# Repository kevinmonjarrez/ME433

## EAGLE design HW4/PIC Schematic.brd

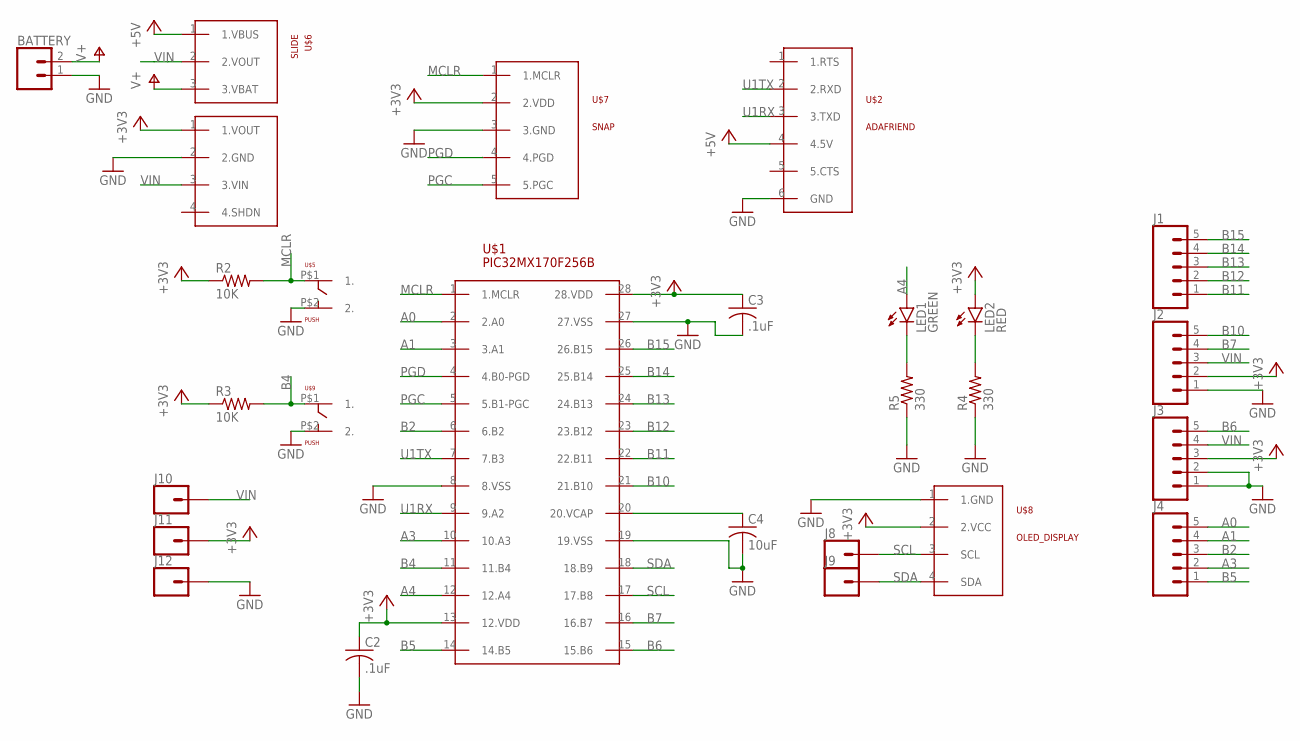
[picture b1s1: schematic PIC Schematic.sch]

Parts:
BATTERY: CONN_02; 1X02
C2, C3: .1uF; C025-030X050
C4: 10uF; C025-030X050
J1, J2, J3, J4: CONN_05; 1X05
J8, J9, J10, J11, J12: CONN_01; 1X01
LED1: GREEN; LED3MM
LED2: RED; LED3MM
R2, R3: 10K; 0207/10
R4, R5: 330; 0207/10
U$1: PIC32MX170F256B; DIL28-3
U$2: ADAFRIEND
U$3: POLOLU_3V3
U$5, U$9: PUSH
U$6: SLIDE
U$7: SNAP
U$8: OLED_DISPLAY

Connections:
+3V3: C2.1, C3.1, J2.2, J3.3, J11.1, LED2.A, R2.1, R3.1, U$1.13 (12.VDD), U$1.28 (28.VDD), U$3.1 (1.VOUT), U$7.2 (2.VDD), U$8.2 (2.VCC)
+5V: U$2.4 (4.5V), U$6.1 (1.VBUS)
A0: J4.5, U$1.2 (2.A0)
A1: J4.4, U$1.3 (3.A1)
A3: J4.2, U$1.10 (10.A3)
A4: LED1.A, U$1.12 (12.A4)
B2: J4.3, U$1.6 (6.B2)
B4: R3.2, U$1.11 (11.B4), U$9.P$1 (1.)
B5: J4.1, U$1.14 (14.B5)
B6: J3.5, U$1.15 (15.B6)
B7: J2.4, U$1.16 (16.B7)
B10: J2.5, U$1.21 (21.B10)
B11: J1.1, U$1.22 (22.B11)
B12: J1.2, U$1.23 (23.B12)
B13: J1.3, U$1.24 (24.B13)
B14: J1.4, U$1.25 (25.B14)
B15: J1.5, U$1.26 (26.B15)
GND: BATTERY.1, C2.2, C3.2, C4.2, J2.1, J3.1, J3.2, J12.1, R4.1, R5.1, U$1.8 (8.VSS), U$1.19 (19.VSS), U$1.27 (27.VSS), U$2.6 (GND), U$3.2 (2.GND), U$5.P$2 (2.), U$7.3 (3.GND), U$8.1 (1.GND), U$9.P$2 (2.)
MCLR: R2.2, U$1.1 (1.MCLR), U$5.P$1 (1.), U$7.1 (1.MCLR)
unnamed: C4.1, U$1.20 (20.VCAP)
unnamed: LED1.K (C), R5.2
unnamed: LED2.K (C), R4.2
PGC: U$1.5 (5.B1-PGC), U$7.5 (5.PGC)
PGD: U$1.4 (4.B0-PGD), U$7.4 (4.PGD)
SCL: J8.1, U$1.17 (17.B8), U$8.3 (SCL)
SDA: J9.1, U$1.18 (18.B9), U$8.4 (SDA)
U1RX: U$1.9 (9.A2), U$2.3 (3.TXD)
U1TX: U$1.7 (7.B3), U$2.2 (2.RXD)
V+: BATTERY.2, U$6.3 (3.VBAT)
VIN: J2.3, J3.4, J10.1, U$3.3 (3.VIN), U$6.2 (2.VOUT)

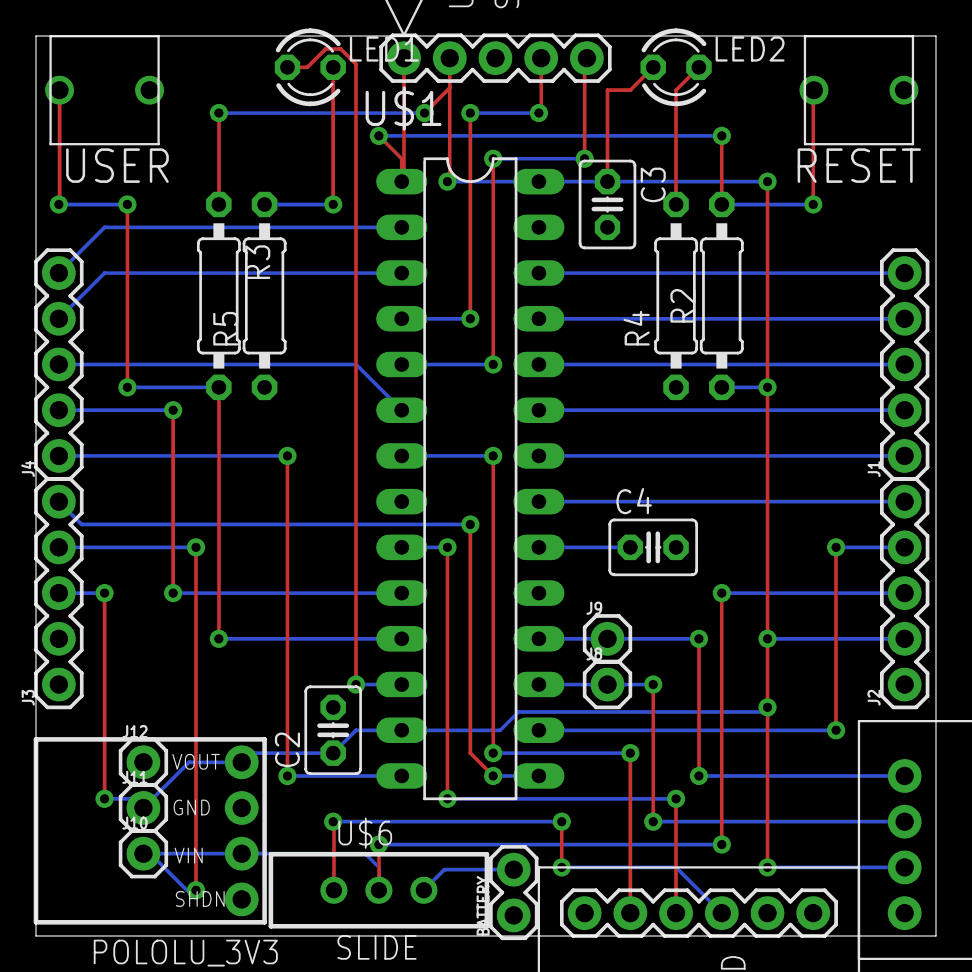
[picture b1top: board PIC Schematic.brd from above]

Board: 2 copper layers, 50.0 x 50.0 mm, 27 parts (0 on the bottom side), 30 nets.

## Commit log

2022-04-04 HW 2 PIC Circuit
2022-04-07 HW3 Changes
2022-04-13 EAGLE PCB
2022-04-21 HW 5 and 6
2022-04-24 HW7 included, most in MPLAB Projects
2022-05-27 A Couple more HW
2022-06-08 Catchin up
2022-06-10 HW 12 Updates
